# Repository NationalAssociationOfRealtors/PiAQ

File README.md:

#PiAQ - Open Source Indoor Air Quality Sensor
An open hardware and software indoor air quality Raspberry Pi HAT provided by the [National Association of REALTORS](http://realtor.org) and [CRT Labs](https://crtlabs.org).

The board comes in two form factors. One dedicated for the Raspberry Pi - [PiAQ](http://piaq.io)

<p align="center">
  
</p>

Measurement Points:

* Temperature (SHT31)
* Relative Humidity (SHT31)
* VOC (Volatile Organic Compounds) (IAQ Core)
* Derived CO2 (IAQ Core)
* Barometric Pressure (MPL3115A2)
* Light Intensity (TSL2561)
* CO Concentration (MiCS-4154)
* NO2 Concentration (MiCS-4154)
* Sound Intensity (ADMP401)

Connectivity:

* FSK (RFM69HW 433/915MHz)
* WiFi (Particle Photon)
* Cellular (Particle Electron) (Coming soon)
* LoRa (Coming Soon)

License:
Apache License Version 2.0

For information on the standalone air quality sensor, <a href="https://github.com/NationalAssociationOfRealtors/IndoorAirQualitySensor">click here.

</a>

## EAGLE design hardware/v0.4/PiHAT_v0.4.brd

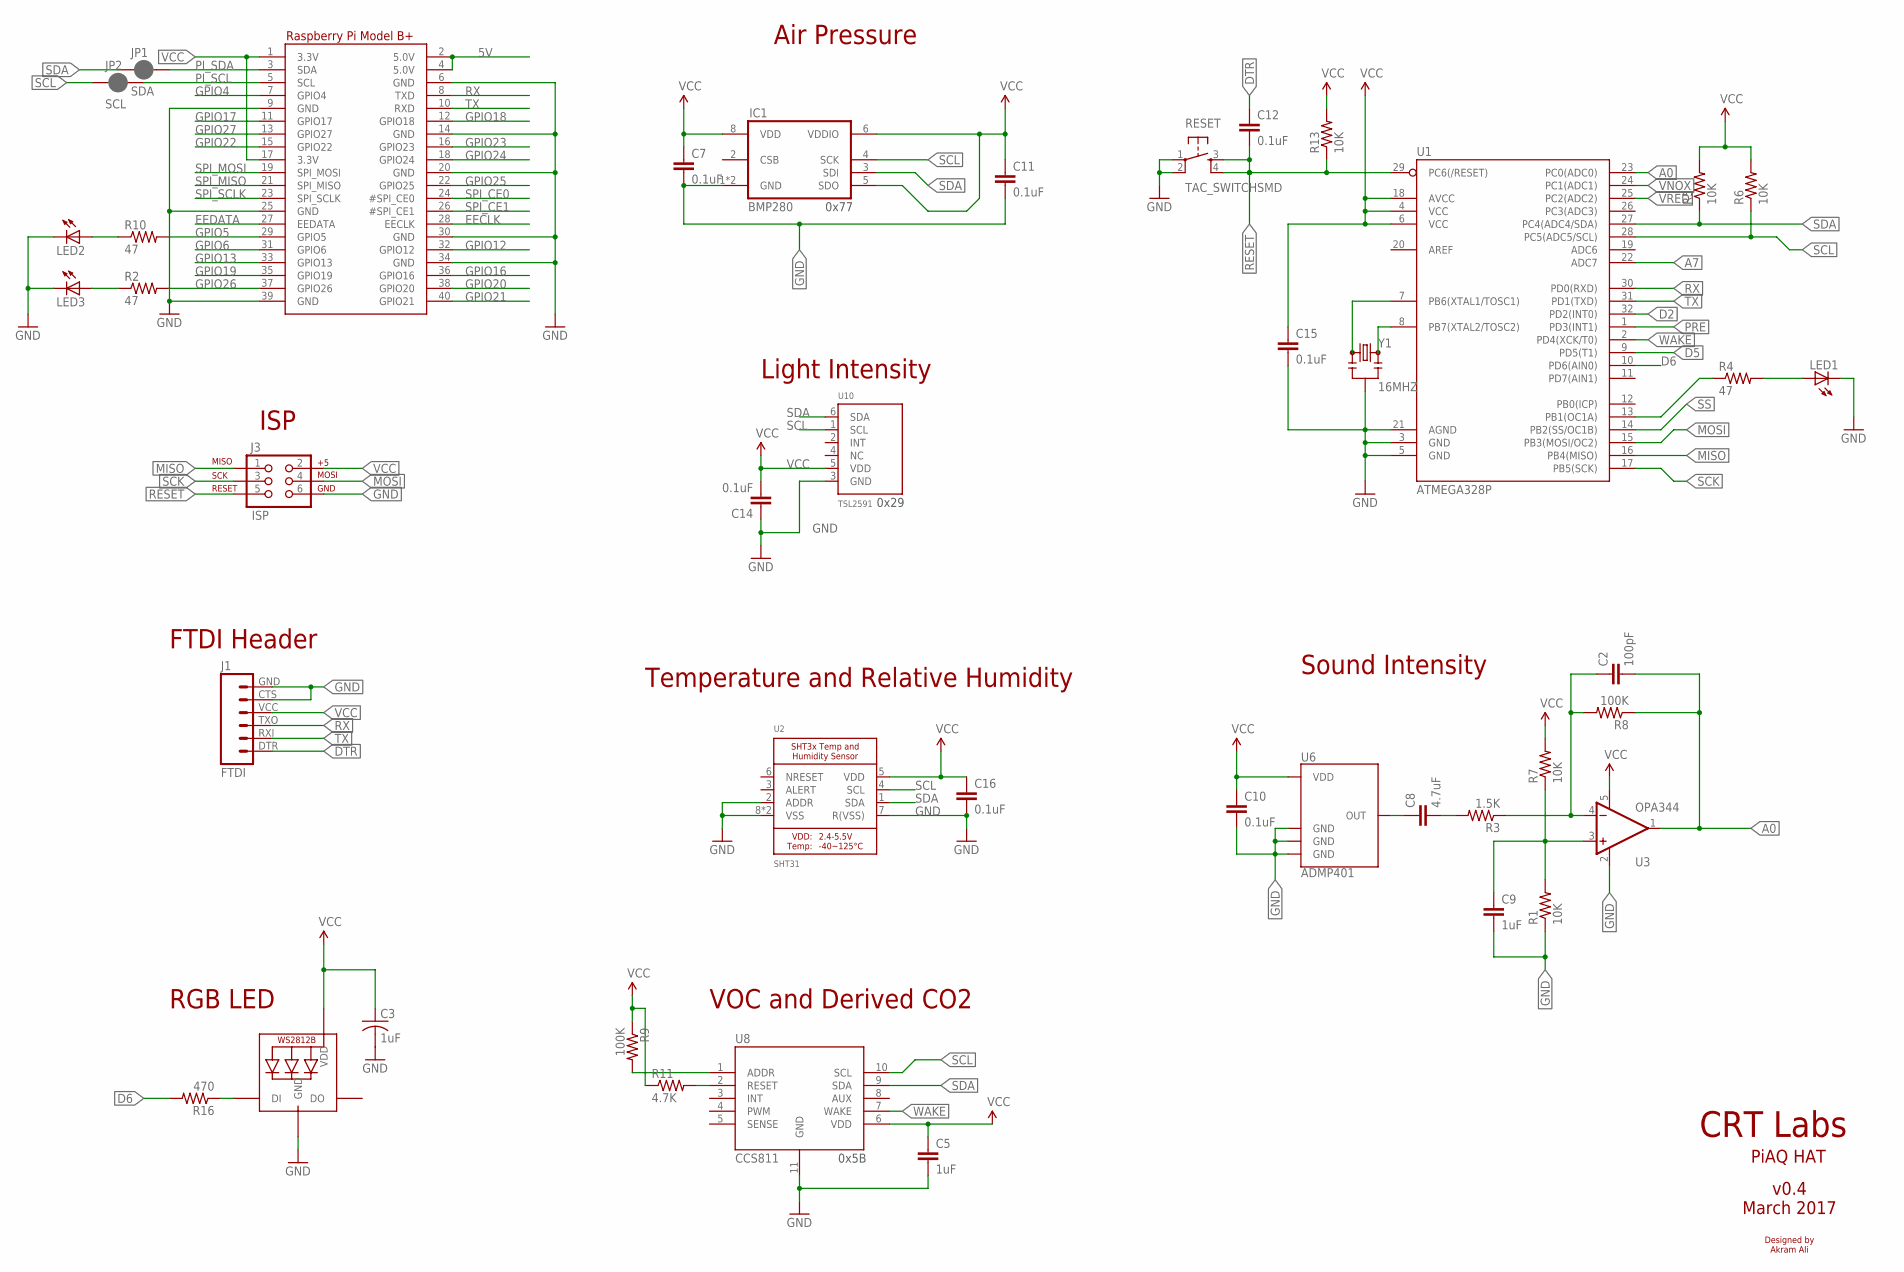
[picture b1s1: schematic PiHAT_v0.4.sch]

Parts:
C2: 100pF; 0805; MPN CC0805JRNPO9BN101
C3: 1uF; C0603K; MPN CC0805ZRY5V8BB105
C5: 1uF; 0805; MPN CC0603KRX7R7BB104
C7, C10, C11, C12, C15: 0.1uF; 0805; MPN CC0603KRX7R7BB104
C8: 4.7uF; 0805; MPN CC0805KKX5R8BB475
C9: 1uF; 0805; MPN CC0805KKX7R7BB105
C14, C16: 0.1uF; 0805; MPN CC0805KRX7R9BB104
IC1: BMP280; MPN BMP280
J1: FTDI; FTDI_BASIC
J3: ISP; 2X3
JP1: SDA; PAD-JUMPER-2-NC_BY_PASTE_YES_SILK_FULL_BOX
JP2: SCL; PAD-JUMPER-2-NC_BY_PASTE_YES_SILK_FULL_BOX
LED1, LED2, LED3: LEDCHIPLED_0805; CHIPLED_0805; MPN LTST-C170TBKT
R1, R5, R6, R7, R13: 10K; 0805; MPN RC0805JR-0710KL
R2, R4, R10: 47; 0805; MPN RC0805JR-0747RL
R3: 1.5K; 0805; MPN RT0805BRD071K5L
R8, R9: 100K; 0805; MPN RC0805FR-07100KL
R11: 4.7K; 0805; MPN RC0805FR-07100KL
R16: 470; R0603; MPN RC0805FR-07470RL
RESET: TAC_SWITCHSMD; TACTILE-SWITCH-SMD; MPN PTS525SM15SMTR2 LFS
RGBLED: WS2812B3535; LED3535; MPN SK6812 mini
RPI1: RASPBERRYPI_BPLUS_HATSLOTS; PI_HAT_SLOTS
U1: ATMEGA328P; TQFP32-08; MPN ATMEGA328PB-AU
U2: SHT31; SHT3X; MPN SHT35-DIS-B
U3: OPA344; SOT23-5; MPN OPA344NA/3K
U6: ADMP401; MPN INMP401ACEZ-R7
U8: CCS811; LGA; MPN CCS811
U10: TSL2591; DFN6_TAOS; MPN TSL25911FN
Y1: 16MHZ; RESONATOR-SMD; MPN CSTCE16M0V53-R0

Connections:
5V: RPI1.2 (5.0V), RPI1.4 (5.0V)
A0: C2.2, R8.1, U1.23 (PC0(ADC0)), U3.1 (OUT)
A7: U1.22 (ADC7)
D2: U1.32 (PD2(INT0))
D5: U1.9 (PD5(T1))
D6: R16.2, U1.10 (PD6(AIN0))
DTR: C12.1, J1.DTR (1)
EECLK: RPI1.28 (EECLK)
EEDATA: RPI1.27 (EEDATA)
GND: C3.2, C5.2, C7.2, C9.2, C10.2, C11.2, C14.1, C15.2, C16.2, IC1.1 (GND), IC1.7 (GND), J1.CTS (5), J1.GND (6), J3.6, LED1.C, LED2.C, LED3.C, R1.1, RESET.1, RESET.2, RGBLED.4 (GND), RPI1.6 (GND), RPI1.9 (GND), RPI1.14 (GND), RPI1.20 (GND), RPI1.25 (GND), RPI1.30 (GND), RPI1.34 (GND), RPI1.39 (GND), U1.3 (GND), U1.5 (GND), U1.21 (AGND), U2.2 (ADDR), U2.7 (R(VSS)), U2.8 (VSS), U2.THERMAL (VSS), U3.2 (V-), U6.2 (GND), U6.4 (GND), U6.6 (GND), U8.11 (GND), U10.3 (GND), Y1.2
GPIO4: RPI1.7 (GPIO4)
GPIO5: R10.2, RPI1.29 (GPIO5)
GPIO6: RPI1.31 (GPIO6)
GPIO12: RPI1.32 (GPIO12)
GPIO13: RPI1.33 (GPIO13)
GPIO16: RPI1.36 (GPIO16)
GPIO17: RPI1.11 (GPIO17)
GPIO18: RPI1.12 (GPIO18)
GPIO19: RPI1.35 (GPIO19)
GPIO20: RPI1.38 (GPIO20)
GPIO21: RPI1.40 (GPIO21)
GPIO22: RPI1.15 (GPIO22)
GPIO23: RPI1.16 (GPIO23)
GPIO24: RPI1.18 (GPIO24)
GPIO25: RPI1.22 (GPIO25)
GPIO26: R2.2, RPI1.37 (GPIO26)
GPIO27: RPI1.13 (GPIO27)
MISO: J3.1, U1.16 (PB4(MISO))
MOSI: J3.4, U1.15 (PB3(MOSI/OC2))
unnamed: LED3.A, R2.1
unnamed: R4.1, U1.13 (PB1(OC1A))
unnamed: LED1.A, R4.2
unnamed: U1.8 (PB7(XTAL2/TOSC2)), Y1.3
unnamed: U1.7 (PB6(XTAL1/TOSC1)), Y1.1
unnamed: LED2.A, R10.1
unnamed: C8.1, U6.1 (OUT)
unnamed: R11.2, U8.2 (RESET)
unnamed: C8.2, R3.2
unnamed: C2.1, R3.1, R8.2, U3.4 (-IN)
unnamed: C9.1, R1.2, R7.1, U3.3 (+IN)
unnamed: R16.1, RGBLED.1 (DI)
unnamed: R9.2, U8.1 (ADDR)
PI_SCL: JP2.2, RPI1.5 (SCL)
PI_SDA: JP1.2, RPI1.3 (SDA)
PRE: U1.1 (PD3(INT1))
RESET: C12.2, J3.5, R13.1, RESET.3, RESET.4, U1.29 (PC6(/RESET))
RX: J1.TXO (3), RPI1.8 (TXD), U1.30 (PD0(RXD))
SCK: J3.3, U1.17 (PB5(SCK))
SCL: IC1.4 (SCK), JP2.1, R6.1, U1.28 (PC5(ADC5/SCL)), U2.4 (SCL), U8.10 (SCL), U10.1 (SCL)
SDA: IC1.3 (SDI), JP1.1, R5.1, U1.27 (PC4(ADC4/SDA)), U2.1 (SDA), U8.9 (SDA), U10.6 (SDA)
SPI_CE0: RPI1.24 (#SPI_CE0)
SPI_CE1: RPI1.26 (#SPI_CE1)
SPI_MISO: RPI1.21 (SPI_MISO)
SPI_MOSI: RPI1.19 (SPI_MOSI)
SPI_SCLK: RPI1.23 (SPI_SCLK)
SS: U1.14 (PB2(SS/OC1B))
TX: J1.RXI (2), RPI1.10 (RXD), U1.31 (PD1(TXD))
VCC: C3.1, C5.1, C7.1, C10.1, C11.1, C14.2, C15.1, C16.1, IC1.5 (SDO), IC1.6 (VDDIO), IC1.8 (VDD), J1.VCC (4), J3.2, R5.2, R6.2, R7.2, R9.1, R11.1, R13.2, RGBLED.2 (VDD), RPI1.1 (3.3V), RPI1.17 (3.3V), U1.4 (VCC), U1.6 (VCC), U1.18 (AVCC), U2.5 (VDD), U3.5 (V+), U6.5 (VDD), U8.6 (VDD), U10.5 (VDD)
VNOX: U1.24 (PC1(ADC1))
VRED: U1.25 (PC2(ADC2))
WAKE: U1.2 (PD4(XCK/T0)), U8.7 (WAKE)

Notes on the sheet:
VOC and Derived CO2
Air Pressure
Sound Intensity
Temperature and Relative Humidity
ISP
CRT Labs
PiAQ HAT
v0.4 March 2017
Designed by Akram Ali
0x5B
FTDI Header
0x77
Light Intensity
0x29
RGB LED

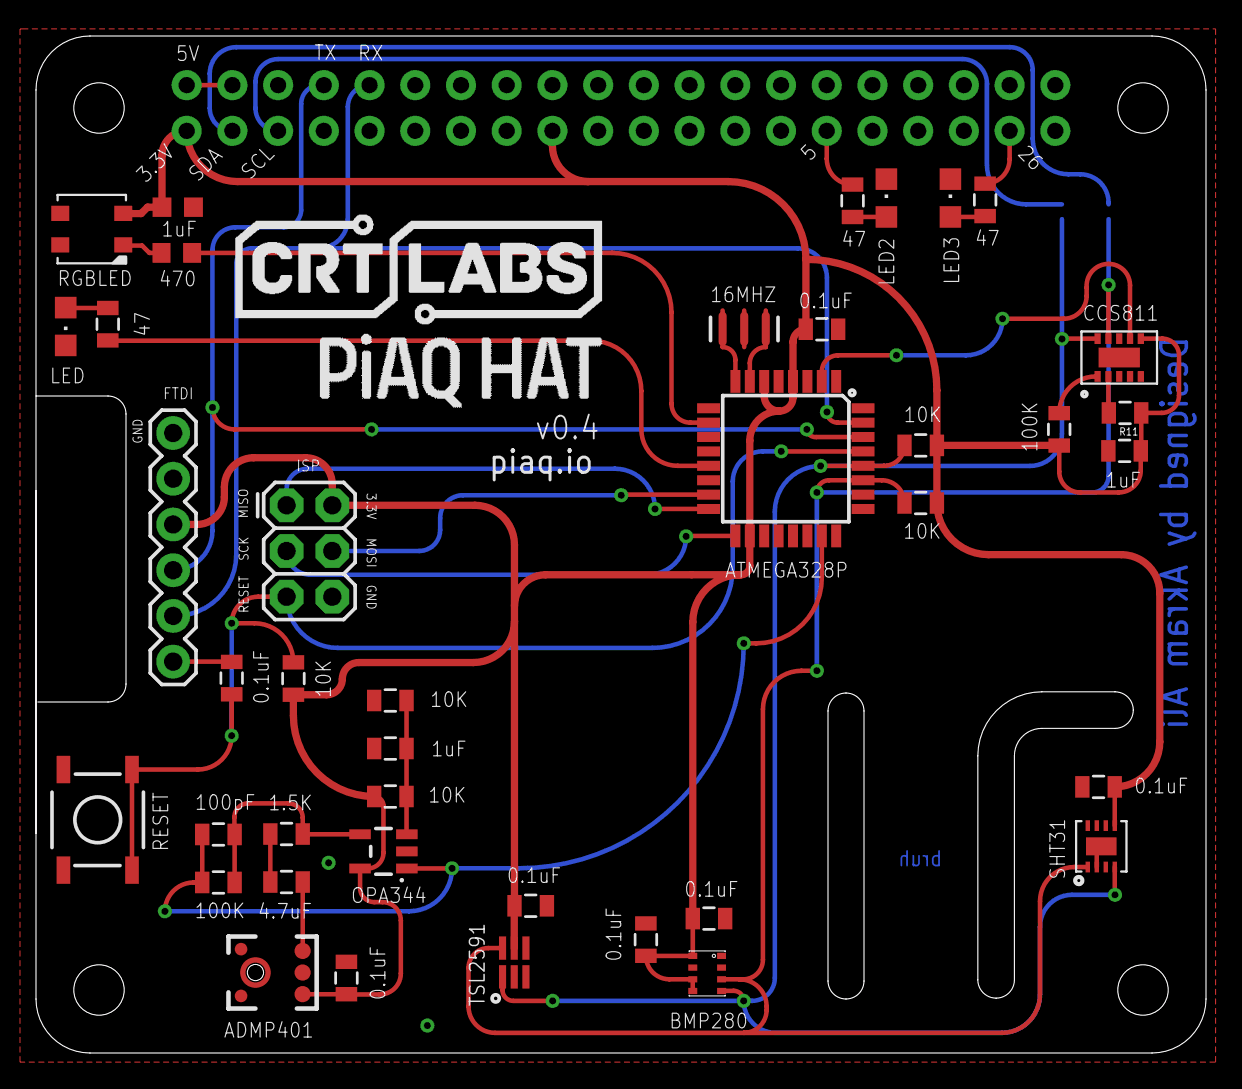
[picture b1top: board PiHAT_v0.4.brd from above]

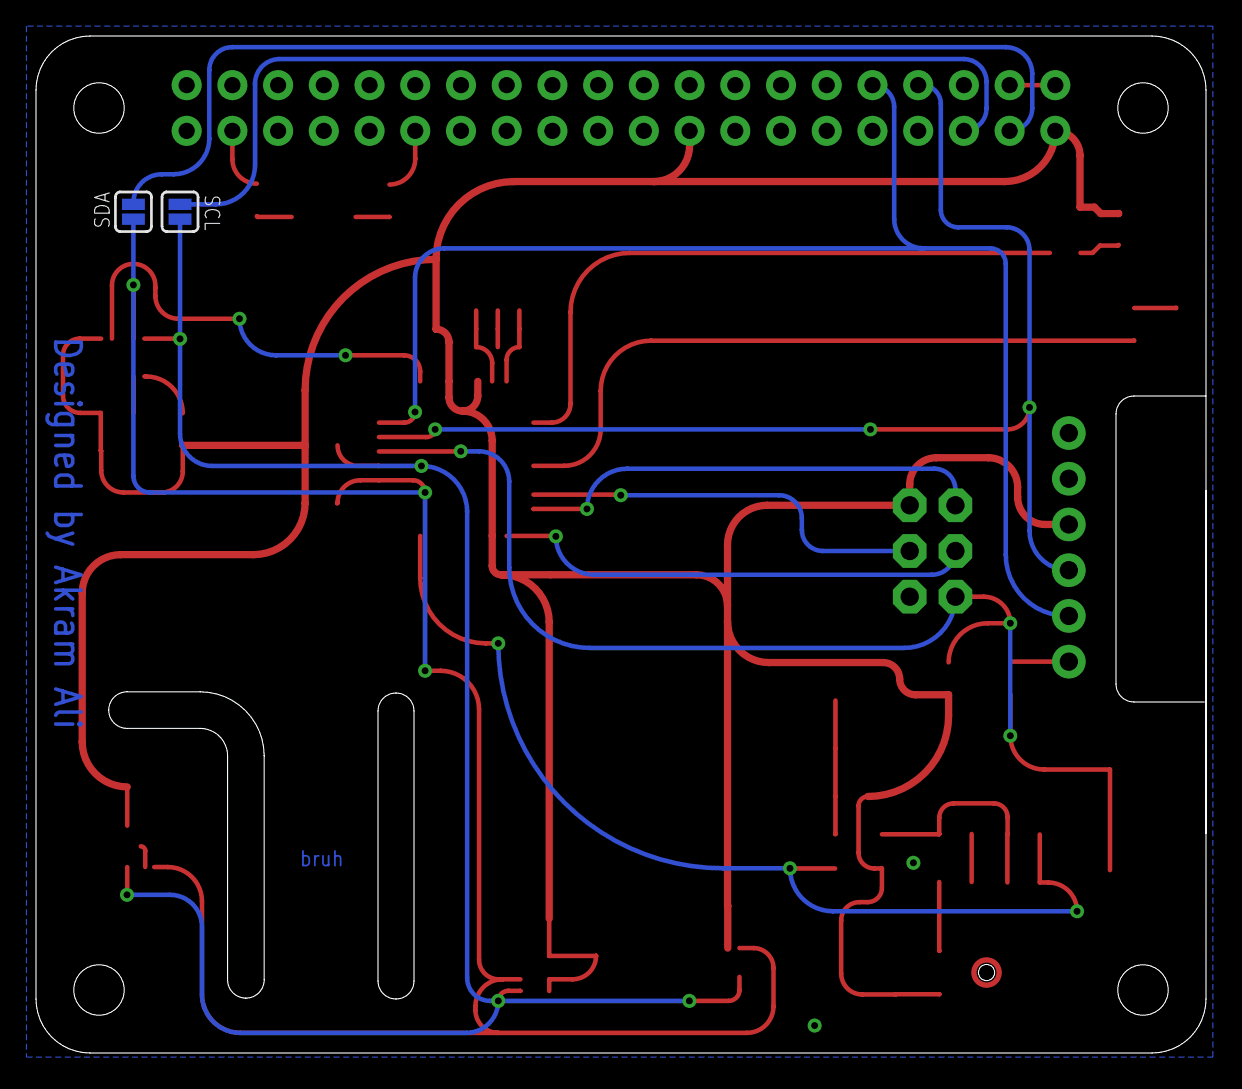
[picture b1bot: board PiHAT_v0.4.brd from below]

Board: 2 copper layers, 65.0 x 56.5 mm, 43 parts (2 on the bottom side), 32 nets.

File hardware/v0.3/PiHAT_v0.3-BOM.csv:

Qty,Value,Device,Package,Parts,Description,MPN
3,,LEDCHIPLED_0805,CHIPLED_0805,LED1- LED2- LED3,LED,LTST-C170TBKT
8,0.1uF,CAP0805,805,C3- C4- C5- C7- C10- C11- C12- C15,Capacitor,CC0603KRX7R7BB104
1,1.5K,RESISTOR0805-RES,805,R3,Resistor,RT0805BRD071K5L
2,100K,RESISTOR0805-RES,805,R8- R9,Resistor,RC0805FR-07100KL
1,100pF,CAP0805,805,C2,Capacitor,CC0805JRNPO9BN101
5,10K,RESISTOR0805-RES,805,R1- R5- R6- R7- R13,Resistor,RC0805JR-0710KL
1,16MHZ,RESONATOR16MHZ,RESONATOR-SMD,Y1,Resonator,CSTCE16M0V53-R0
1,1uF,CAP0805,805,C9,Capacitor,CC0805KKX7R7BB105
1,4.7uF,CAP0805,805,C8,Capacitor,CC0805KKX5R8BB475
3,47,RESISTOR0805-RES,805,R2- R4- R10,Resistor,RC0805JR-0747RL
1,ADMP401,ADMP401,ADMP401,U6,Omnidirection bottom-port MEMS microphone,INMP401ACEZ-R7
1,ATMEGA328P,ATMEGA328P_TQFP,TQFP32-08,U1,MCU,ATMEGA328PB-AU
1,BMP280,BMP280,BMP280,IC1,Barometric pressure sensor,BMP280
1,CCS811,CCS811-I2C,LGA,U8,Digital Gas Sensor,CCS811
1,OPA344,OPA344,SOT23-5,U3,Single gate rail-to-rail output op-amp. Inputs extend 300mV past rails.,OPA344NA/3K
1,SHT31/35,SHT31-DIS,SHT3X,U7,Temperature and Humidity,SHT31-DIS-B
1,TAC_SWITCHSMD,TAC_SWITCHSMD,TACTILE-SWITCH-SMD,RESET,Momentary Switch,PTS525SM15SMTR2 LFS
1,TSL2561,TSL2561FN,FN-6,U2,TSL2561 illumination sensor,TSL2561FN

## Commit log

2016-10-18 Revert "Update index.html"
    This reverts commit bed5db49b7a3c8d1d036d5b4aa98a6fe2bd997f5.
2016-10-18 moving piaq to standalone repo
    leaving sensor board in previous repo
2016-10-19 Updating Links to point at new repo
2016-10-19 clarifying language regarding PiAQ separation
2016-10-19 replacing spreadsheet with octopart list
2016-10-19 fixing broken links
2016-10-19 linking to v2 of board from osh park
2016-10-19 removing documents related to sensor board
2016-10-19 adding mission statement
2016-10-19 wordsmithing mission statement
2016-10-19 unfortunate typo
2016-10-19 removing sensor board firmware
2016-12-09 PiAQ v0.3 - design update
    Added CCS811 CO2/VOC sensor (replaced IAQ core)
    Added BMP280 pressure sensor (replaced MPL3115A2)
    Connected I2C pins from ATmega328P to RPi I2C pins
    Rewired everything using rounded traces
2016-12-09 Some trace adjustments
2016-12-09 Added jumpers on the I2C line
    Jumpers between Pi's SDA and SCL lines and ATmega's SDA and SCL lines
2016-12-09 Changed silkscreen to tPlace/bPlace layers
    from 121/122 to 21/22
2016-12-09 OSH park render
2016-12-12 BOM adjustments
2016-12-12 Updated all attributes for BOM
    Fixed digikey and mouser numbers
2016-12-12 Added gerber files
2016-12-12 Updated LED attributes
    Changed MPN from 0603 to 0805 part
2016-12-12 adding compressed gerber files
2016-12-12 adding BOM
2016-12-12 Removed Digikey and Mouser numbers to avoid confusion
2017-03-07 v0.4 added [WIP]
2017-03-07 v0.4 - update
    Relocated SHT31/35 sensor location to be on a 'cooler' spot over the Pi
    Added extra rullup resistor on CCS811 to make it stable during startups
    trace adjustments
2017-03-13 Adjusted silkscreen
2017-03-13 Added RGB LED
    - RGB LED on pin 6
    - Rearragned other LED on pin 9 and adjusted trace
2017-05-08 Moved folders
2017-06-14 cleaned up the repo
    removed all raw images
2018-02-28 Create LICENSE

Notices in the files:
parts and their libraries:
microbuilder: This work is placed in the public domain, and may be freely used for commercial and non-commercial work with the following conditions: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
SparkFun-DigitalIC: Licensing: Creative Commons ShareAlike 4.0 International - https://creativecommons.org/licenses/by-sa/4.0
